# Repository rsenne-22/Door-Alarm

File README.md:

# ESP32 Door Alarm

A simple door-monitoring alarm built on an ESP32. A reed switch detects when the door is opened, and if the door opens **without** the disarm button being pressed, the buzzer sounds and the LED lights up until the door is closed (or the button is pressed to silence it).

# About
This is a personal hobby project built to explore embedded systems and IoT fundamentals. This project idea came to me as a device to alert me and my family if my little brother opens the front door and tries to leave by himself. 

# Skills Demonstrated
1. Embedded C/C++ programming on ESP32 (Arduino framework)
2. Digital I/O: reading sensors (reed switch, button) and driving outputs (buzzer, LED)
3. Basic state machine design (armed / disarmed / triggered)
4. Circuit design and wiring (pull-up resistors, current limiting, switch debouncing)
5. Debugging and iterative hardware testing

## How It Works

1. The **door reed sensor** detects the open/closed state of the door.
2. Pressing the **button** disarms the alarm for a set window (when you want to open the door normally).
3. If the door opens while the system is **armed** (button not pressed), the **active buzzer** and **LED** turn on.
4. Closing the door and/or pressing the button resets the alarm back to idle state.

## Hardware

| Component | Purpose |
|---|---|
| ESP32 dev board | Main microcontroller |
| Reed switch + magnet | Detects door open/closed |
| Push button | Disarms the alarm before opening the door |
| Active buzzer | Audible alert |
| LED | Visual alert |
| Resistors | Pull-up/pull-down for button and reed switch, current-limiting for LED |

## Behavior / Logic

- **Idle/Armed:** Door closed, system waiting.
- **Disarm:** Button press starts a grace period during which opening the door does *not* trigger the alarm.
- **Triggered:** Door opens while armed → buzzer + LED turn on.
- **Reset:** Door closes again, and/or button is pressed, silences the buzzer/LED and returns to idle.

## Possible Improvements

- Add a delay/timeout so the buzzer auto-silences after a set time.
- Add Wi-Fi notifications (e.g., push notification) when triggered.
- Add a status LED for "armed" vs "disarmed" state.
- Battery-power the unit with a low-power sleep mode between checks.
- Custom PCB to make the project permanent.
- 3D-printed casing for the PCB.

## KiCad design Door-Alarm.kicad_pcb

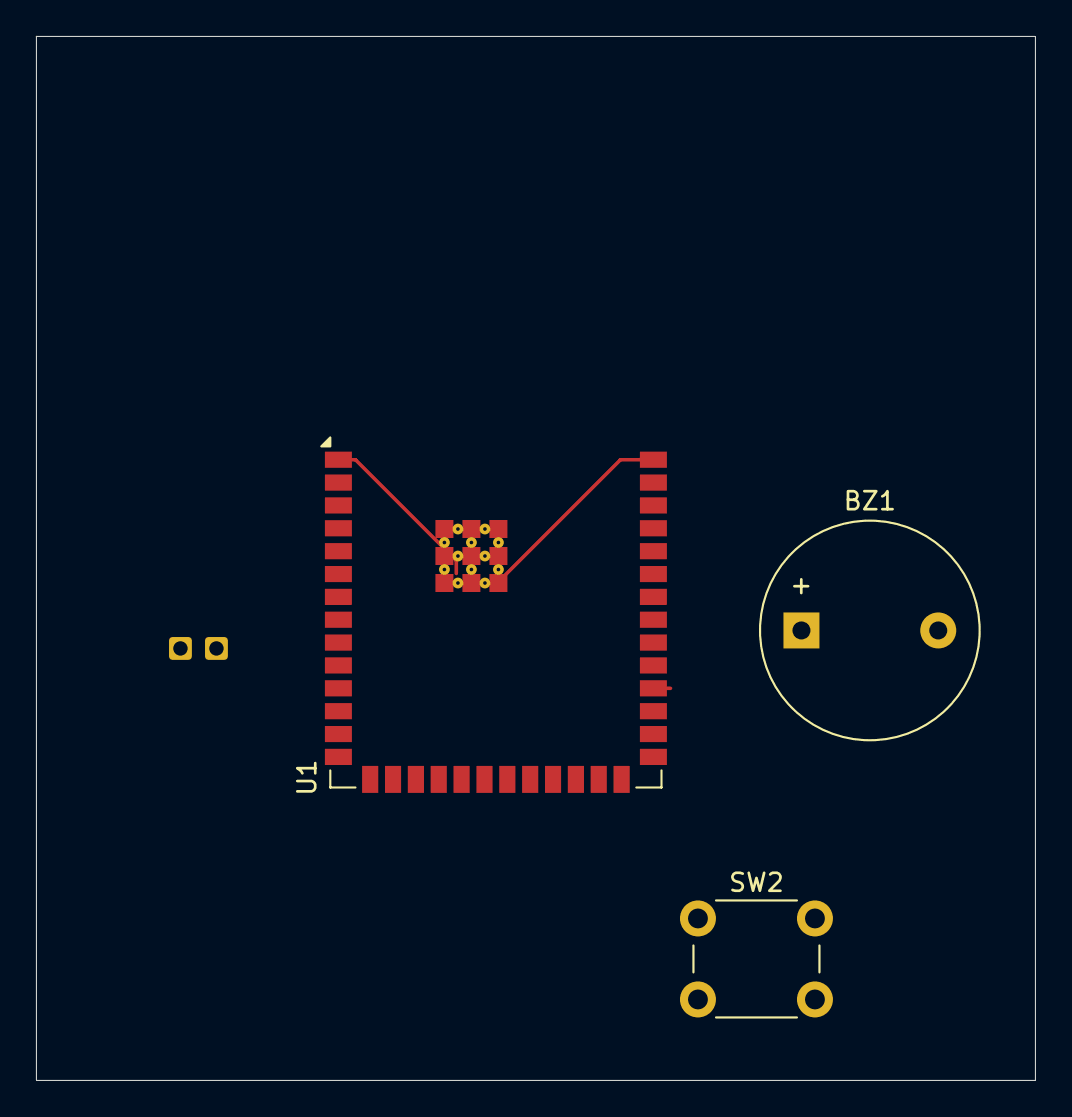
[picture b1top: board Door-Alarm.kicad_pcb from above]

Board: 2 copper layers, 55.5 x 58.0 mm, 4 parts (0 on the bottom side), 4 nets.

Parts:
BZ1: Buzzer; Buzzer_12x9.5RM7.6
SW1: SW_Reed; Door_SW
SW2: SW_Push; SW_PUSH_6mm
U1: ESP32-S3-WROOM-1; ESP32-S3-WROOM-2

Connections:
unnamed: BZ1.1 (+), U1.34 (IO41)
unnamed: BZ1.2 (-), SW1.2, SW2.2, U1.1 (GND), U1.40 (GND), U1.41 (GND)
unnamed: SW1.1, U1.30 (IO37)
unnamed: SW2.1, U1.35 (IO42)
